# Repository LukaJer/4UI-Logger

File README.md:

# 4UI-Logger

## 16-bit 4 Channel Voltage and Current Logger

### Hardware Desctiption:  
- Voltage ADC: TI ADS1115
- Current ADC: TI INA228

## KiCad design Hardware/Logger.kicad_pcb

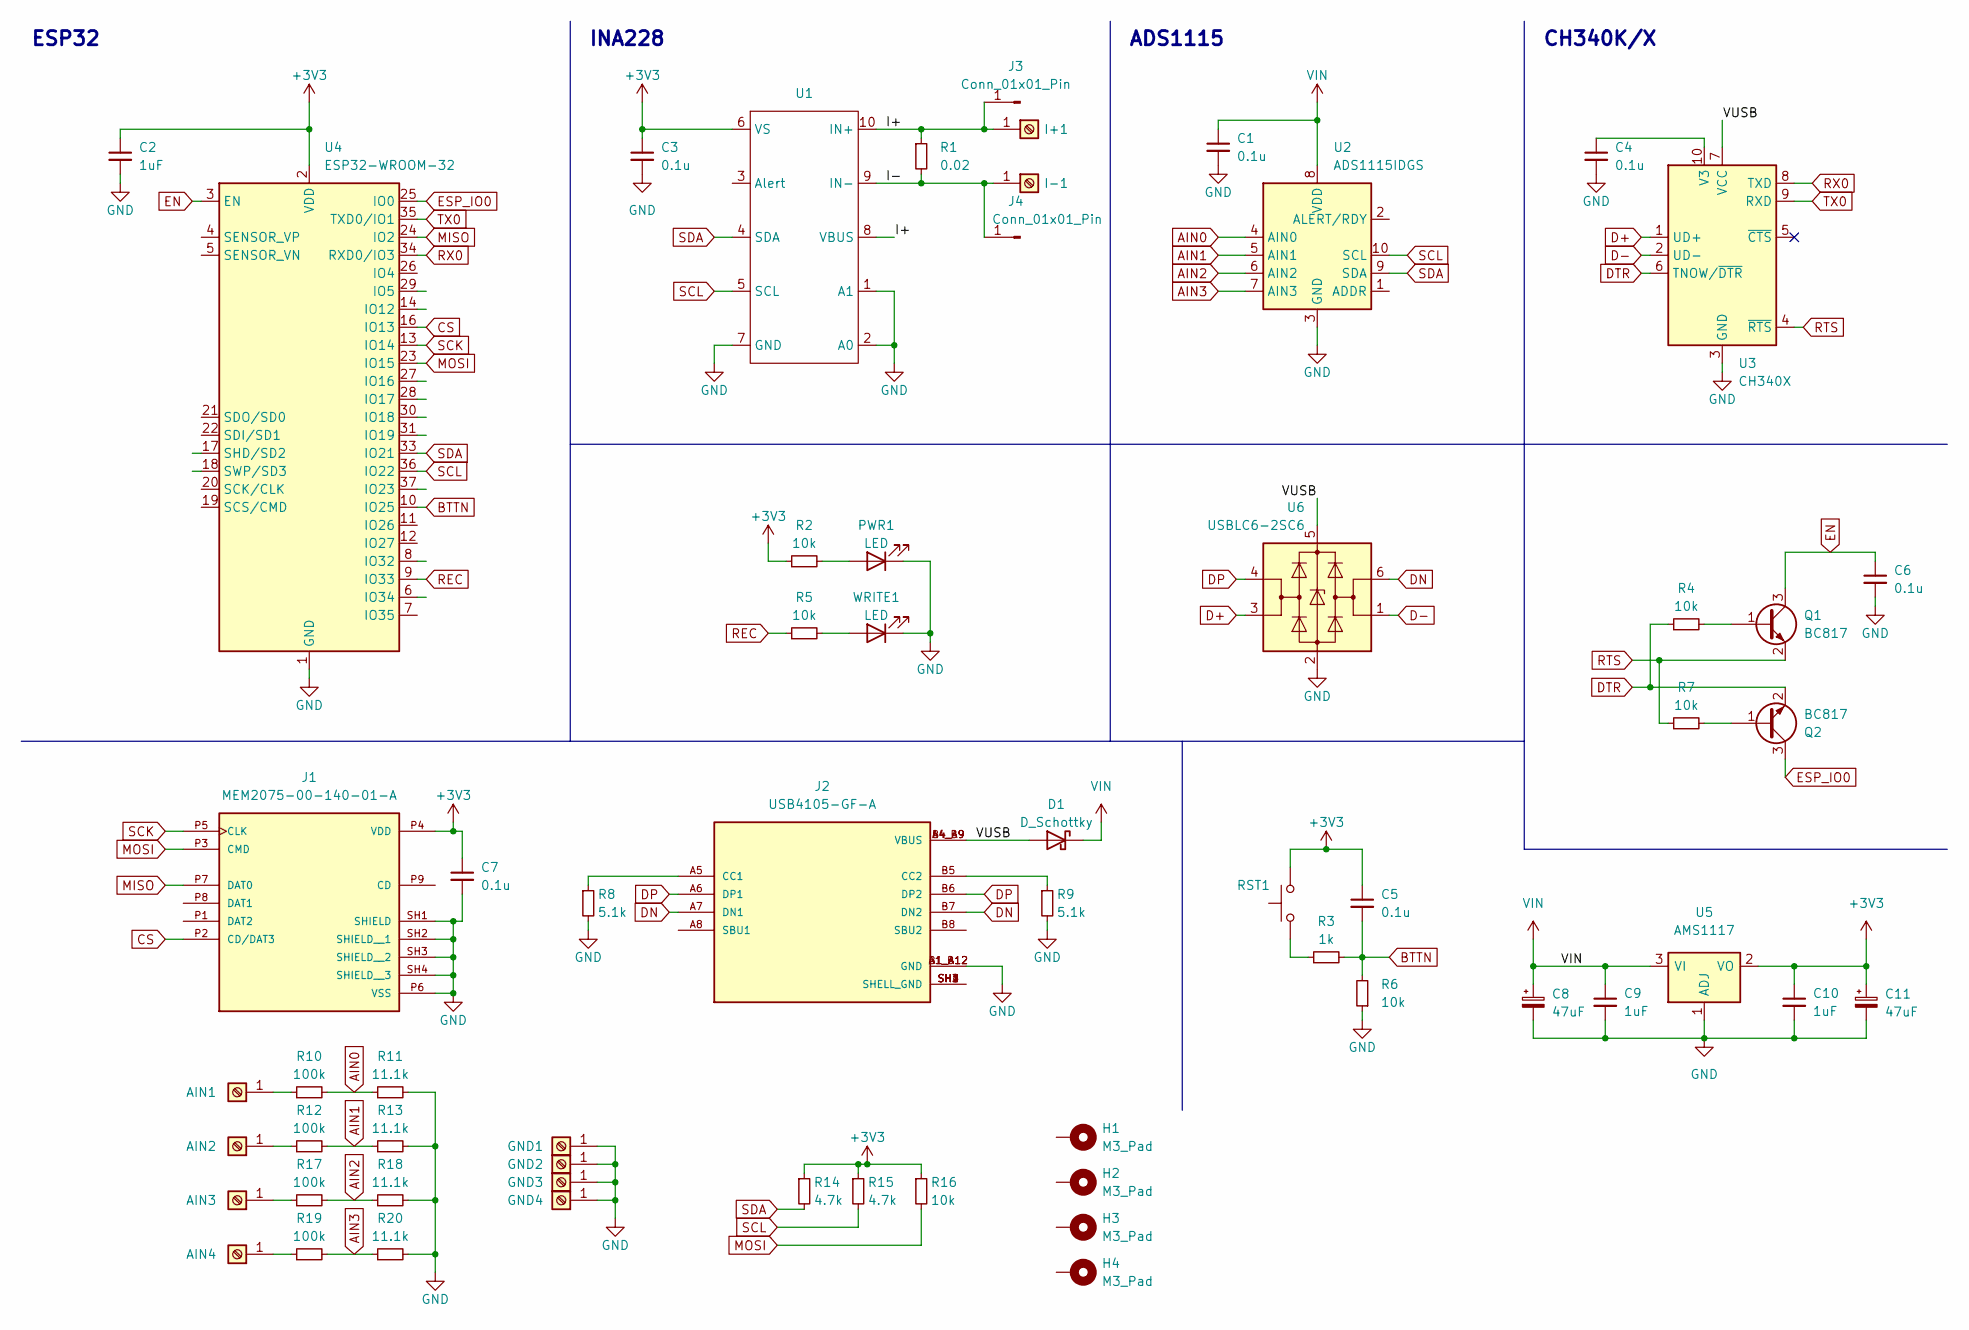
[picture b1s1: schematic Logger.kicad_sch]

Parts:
AIN1, AIN2, AIN3, AIN4: Screw_Terminal_01x01; MountingHole_4.3mm_M4_DIN965_Pad
C1, C3, C4, C5, C6, C7: 0.1u; R_0805_2012Metric
C2: 1uF; C_0805_2012Metric
C8, C11: 47uF; CP_Elec_5x5.3
C9, C10: 1uF; C_1206_3216Metric
D1: D_Schottky; Nexperia_CFP3_SOD-123W
GND1, GND2, GND3, GND4: Screw_Terminal_01x01; MountingHole_4.3mm_M4_DIN965_Pad
H1, H2, H3, H4: M3_Pad; MountingHole_3.2mm_M3_DIN965_Pad
I+1: Screw_Terminal_01x01; MountingHole_4.3mm_M4_DIN965_Pad
I-1: Screw_Terminal_01x01; MountingHole_4.3mm_M4_DIN965_Pad
J1: MEM2075-00-140-01-A; GCT_MEM2075-00-140-01-A; PARTREV A
J2: USB4105-GF-A; GCT_USB4105-GF-A; PARTREV B3; DigiKey_Part_Number 2073-USB4105-GF-ATR-ND
J3, J4: Conn_01x01_Pin; PinHeader_1x01_P1.00mm_Vertical
PWR1: LED; LED_1206_3216Metric
Q1, Q2: BC817; SOT-23
R1: 0.02; R_2512_6332Metric
R2, R4, R5, R6, R7, R16: 10k; R_0805_2012Metric
R3: 1k; R_0805_2012Metric
R8, R9: 5.1k; R_0805_2012Metric
R10, R12, R17, R19: 100k; R_0805_2012Metric
R11, R13, R18, R20: 11.1k; R_0805_2012Metric
R14, R15: 4.7k; R_0805_2012Metric
RST1: SW_Push; SW_Push_SPST_NO_Alps_SKRK
U1: VSSOP-10_3x3mm_P0.5mm
U2: ADS1115IDGS; TSSOP-10_3x3mm_P0.5mm
U3: CH340X; MSOP-10_3x3mm_P0.5mm
U4: ESP32-WROOM-32
U5: AMS1117; SOT-223-3_TabPin2
U6: USBLC6-2SC6; SOT-23-6
WRITE1: LED; LED_1206_3216Metric

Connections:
+3V3: C2.1, C3.1, C5.1, C7.1, C10.1, C11.1, J1.P4 (VDD), R2.1, R14.1, R15.1, R16.1, RST1.2, U1.6 (VS), U4.2 (VDD), U5.2 (VO)
/I+: I+1.1, J3.1, R1.1, U1.8 (VBUS), U1.10 (IN+)
/I-: I-1.1, J4.1, R1.2, U1.9 (IN-)
/VUSB: D1.2 (A), J2.A4_B9 (VBUS), J2.B4_A9 (VBUS), U3.7 (VCC), U6.5 (VBUS)
AIN0: R10.2, R11.1, U2.4 (AIN0)
AIN1: R12.2, R13.1, U2.5 (AIN1)
AIN2: R17.2, R18.1, U2.6 (AIN2)
AIN3: R19.2, R20.1, U2.7 (AIN3)
BTTN: C5.2, R3.2, R6.2, U4.10 (IO25)
CS: J1.P2 (CD/DAT3), U4.16 (IO13)
D+: U3.1 (UD+), U6.3 (I/O2)
D-: U3.2 (UD-), U6.1 (I/O1)
DN: J2.A7 (DN1), J2.B7 (DN2), U6.6 (I/O1)
DP: J2.A6 (DP1), J2.B6 (DP2), U6.4 (I/O2)
DTR: Q2.2 (E), R4.1, U3.6 (TNOW/~DTR)
EN: C6.1, Q1.3 (C), U4.3 (EN)
ESP_IO0: Q2.3 (C), U4.25 (IO0)
GND: C1.2, C2.2, C3.2, C4.2, C6.2, C7.2, C8.2, C9.2, C10.2, C11.2, GND1.1, GND2.1, GND3.1, GND4.1, J1.P6 (VSS), J1.SH1 (SHIELD), J1.SH2 (SHIELD__1), J1.SH3 (SHIELD__2), J1.SH4 (SHIELD__3), J2.A1_B12 (GND), J2.B1_A12 (GND), PWR1.1 (K), R6.1, R8.2, R9.2, R11.2, R13.2, R18.2, R20.2, U1.1 (A1), U1.2 (A0), U1.7 (GND), U2.3 (GND), U3.3 (GND), U4.1 (GND), U4.15 (GND), U4.38 (GND), U4.39 (GND), U5.1 (ADJ), U6.2 (GND), WRITE1.1 (K)
MISO: J1.P7 (DAT0), U4.24 (IO2)
MOSI: J1.P3 (CMD), R16.2, U4.23 (IO15)
unnamed: AIN1.1, R10.1
unnamed: AIN2.1, R12.1
unnamed: AIN3.1, R17.1
unnamed: AIN4.1, R19.1
unnamed: J2.A5 (CC1), R8.1
unnamed: J2.B5 (CC2), R9.1
unnamed: J2.SH1 (SHELL_GND), J2.SH2 (SHELL_GND), J2.SH3 (SHELL_GND), J2.SH4 (SHELL_GND)
unnamed: PWR1.2 (A), R2.2
unnamed: Q1.1 (B), R4.2
unnamed: Q2.1 (B), R7.2
unnamed: R3.1, RST1.1
unnamed: C4.1, U3.10 (V3)
unnamed: R5.2, WRITE1.2 (A)
REC: R5.1, U4.9 (IO33)
RTS: Q1.2 (E), R7.1, U3.4 (~RTS)
RX0: U3.8 (TXD), U4.34 (RXD0/IO3)
SCK: J1.P5 (CLK), U4.13 (IO14)
SCL: R15.2, U1.5 (SCL), U2.10 (SCL), U4.36 (IO22)
SDA: R14.2, U1.4 (SDA), U2.9 (SDA), U4.33 (IO21)
TX0: U3.9 (RXD), U4.35 (TXD0/IO1)
VDD: C1.1, C8.1, C9.1, D1.1 (K), U2.8 (VDD), U5.3 (VI)

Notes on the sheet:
ESP32
INA228
ADS1115
CH340K/X

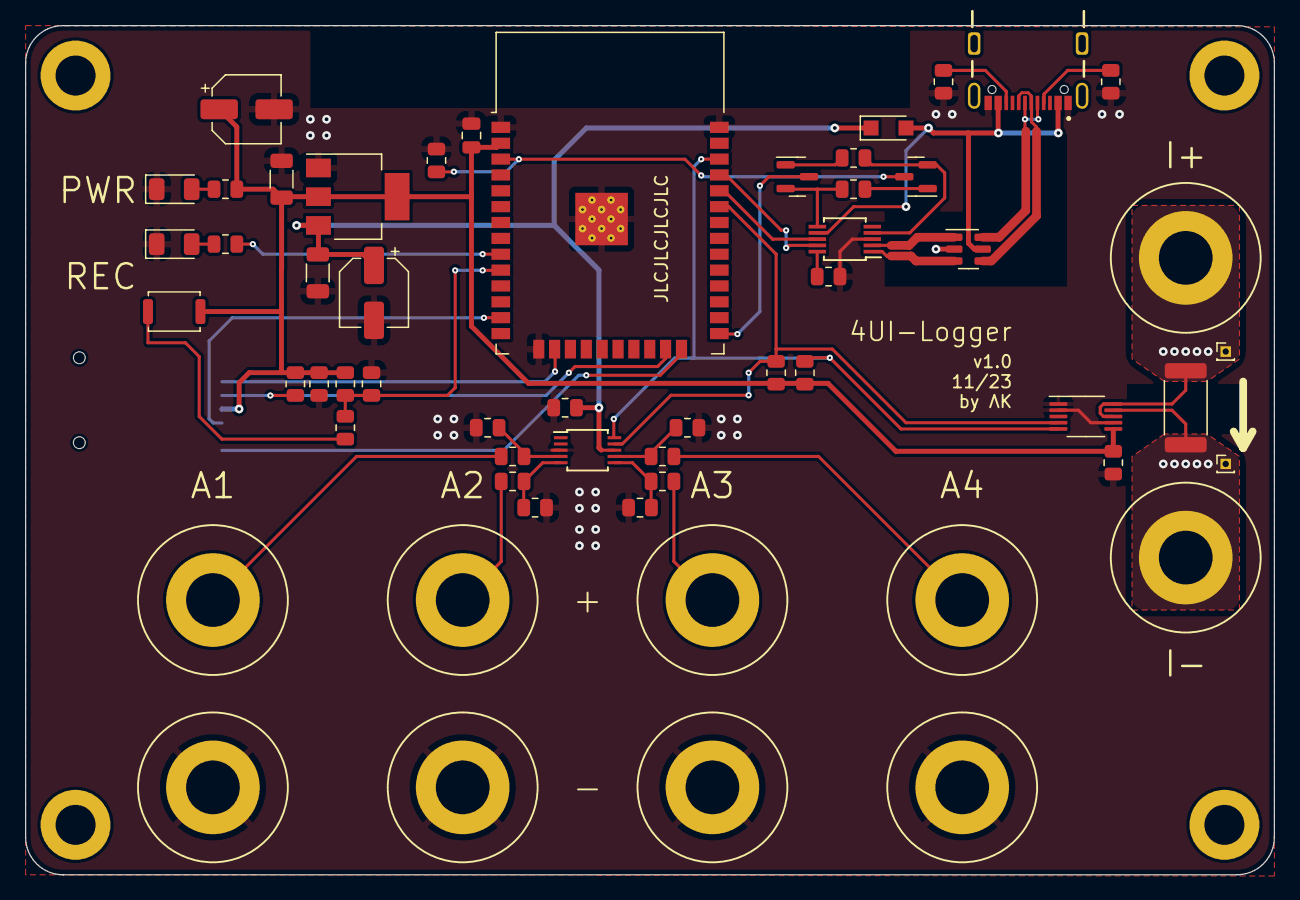
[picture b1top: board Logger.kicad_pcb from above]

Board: 2 copper layers, 100.0 x 68.0 mm, 61 parts (1 on the bottom side), 41 nets.

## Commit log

2023-12-09 init
